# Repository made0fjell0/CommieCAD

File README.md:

<!-- PROJECT LOGO -->
<br />
<div align="center">

<h3 align="center">CommieCAD</h3>

  <p align="center">
    A custom CAD controller (intended for Fusion360) make using <a href="https://hackpad.hackclub.com">Hackpad</a>!
    <br />
    <br />
  </p>
</div>

<!-- TABLE OF CONTENTS -->
<details>
  <summary>Table of Contents</summary>
  <ol>
    <li>
      <a href="#about-the-project">About The Project</a>
    </li>
    <li>
      <a href="#How to">How to</a>
      <ul>
        <li><a href="#PCB">PCB</a></li>
        <li><a href="#Assembly">Assembly</a></li>
        <li><a href="#Code">Code</a></li>
      </ul>
    </li>
    <li><a href="#license">License</a></li>
  </ol>
</details>

<!-- ABOUT THE PROJECT -->
## About The Project

I had a need for an assistant to help me with design work in Fusion360 because using a touchpad to clumsily navigate around my parts forever is not very nice. This controller will have the following functions: **Orbit/Pan with joystick, zoom with rotary encoder, F, E and C keys for easy hotkey access.**

<!-- GETTING STARTED -->
## How to

First, you will have to 3d print a two part <a href="https://github.com/made0fjell0/CommieCAD/tree/main/STLs">case</a>.

You also need to print a simple <a href="https://github.com/made0fjell0/CommieCAD/blob/main/STLs/Joiner.stl">connective piece</a> between the encoder and joystick.

**IF YOU WANT TO** support me on printables, you can also find the STLs <a href="https://www.printables.com/model/1827930-commiecad">here</a>.

### PCB
**PCB-Less version coming SOON**<br>
The gerbers are <a href="https://github.com/made0fjell0/CommieCAD/tree/main/gerbers">HERE</a> and their compressed version <a href="https://github.com/made0fjell0/CommieCAD/tree/main/production/gerbers.zip">HERE.</a>
<br>
You can get the board cut from <a href="https://jlcpcb.com/pcb-fabrication/fr4-pcb">JLCPCB</a> probably for under 10 or 15$. Just sumbit the <a href="https://github.com/made0fjell0/CommieCAD/raw/refs/heads/main/production/gerbers.zip?raw=true">zip file</a> and they will cut it.
<br><br>
**Schematic**

### Assembly

First, you need to consult the <a href="https://github.com/made0fjell0/CommieCAD/blob/main/BOM.csv">BOM</a> (open it in excel) and get all the necesarry parts.
<br>
| Item Name                           | Qty | Price (total) (EUR) | Item link                                                                                                                                                                                                                                                                                                                                                                                                                                                                                                                                                                                                                                                                     |
|-------------------------------------|-----|---------------------|-------------------------------------------------------------------------------------------------------------------------------------------------------------------------------------------------------------------------------------------------------------------------------------------------------------------------------------------------------------------------------------------------------------------------------------------------------------------------------------------------------------------------------------------------------------------------------------------------------------------------------------------------------------------------------|
| 10-piece Cherry MX Brown switch kit | 1   | $4.58               | https://www.aliexpress.com/item/1005007891400560.html?spm=a2g0o.productlist.main.1.6632471082oz75&algo_pvid=cc87eb31-2a04-4b75-8094-35904d8a1e38&algo_exp_id=cc87eb31-2a04-4b75-8094-35904d8a1e38-0&pdp_ext_f=%7B"order"%3A"548"%2C"spu_best_type"%3A"price"%2C"eval"%3A"1"%2C"fromPage"%3A"search"%7D&pdp_npi=6%40dis%21EUR%214.58%214.58%21%21%2134.98%2134.98%21%4021613b2717880804173645049e10b2%2112000042740647794%21sea%21SK%216159834576%21X%211%210%21n_tag%3A-29919%3Bd%3A96cef531%3Bm03_new_user%3A-29895&curPageLogUid=I1Bh7Q49Hqvc&utparam-url=scene%3Asearch%7Cquery_from%3A%7Cx_object_id%3A1005007891400560%7C_p_origin_prod%3A                               |
| EC11 Rotary Encoder                 | 1   | $2.21               | https://www.aliexpress.com/item/1005006761212564.html?spm=a2g0o.productlist.main.50.29da2f4feu9XAI&algo_pvid=f01df35c-01d2-4d27-9c51-af2cd1076af7&algo_exp_id=f01df35c-01d2-4d27-9c51-af2cd1076af7-49&pdp_ext_f=%7B"order"%3A"107"%2C"eval"%3A"1"%2C"fromPage"%3A"search"%7D&pdp_npi=6%40dis%21EUR%211.67%211.67%21%21%2112.73%2112.72%21%402103962917880806218548881e10ef%2112000038303345963%21sea%21SK%216159834576%21X%211%210%21n_tag%3A-29919%3Bd%3A96cef531%3Bm03_new_user%3A-29895&curPageLogUid=YS14es0NDtm3&utparam-url=scene%3Asearch%7Cquery_from%3A%7Cx_object_id%3A1005006761212564%7C_p_origin_prod%3A                                                         |
| Joystick                            | 1   | $1.88               | https://www.aliexpress.com/item/1005008937490649.html?spm=a2g0o.productlist.main.21.3da072ecLABGBB&algo_pvid=135f1916-67c1-4bf8-8561-105024952dd0&algo_exp_id=135f1916-67c1-4bf8-8561-105024952dd0-20&pdp_ext_f=%7B"order"%3A"3448"%2C"spu_best_type"%3A"price"%2C"eval"%3A"1"%2C"fromPage"%3A"search"%7D&pdp_npi=6%40dis%21EUR%212.40%212.33%21%21%2118.36%2117.81%21%40210381f017880808031036287e0ea1%2112000047277002614%21sea%21SK%216159834576%21X%211%210%21n_tag%3A-29919%3Bd%3A96cef531%3Bm03_new_user%3A-29895%3BpisId%3A5000000215888387&curPageLogUid=N5SeqCFrkKCS&utparam-url=scene%3Asearch%7Cquery_from%3A%7Cx_object_id%3A1005008937490649%7C_p_origin_prod%3A |
| Keycaps                             | 3   | N/A                 | Find any set you like or get some spares from a keyboard.                                                                                                                                                                                                                                                                                                                                                                                                                                                                                                                                                                                                                     |
| Seeedstudio XIAO RP2040             | 1   | $3.99               | https://www.seeedstudio.com/XIAO-RP2040-v1-0-p-5026.html                                                                                                                                                                                                                                                                                                                                                                                                                                                                                                                                                                                                                      |
| M3 Screws 25mm screws               | 4   | $5.25               |                                                                                                                                                                                                                                                                                                                                                                                                                                                                                                                                                                                                                                                                               |
| Total Price (EUR): 17.91€           |     |                     |                                                                                                                                                                                                                                                                                                                                                                                                                                                                                                                                                                                                                                                                               |
<br>
Let the assembly begin: <br>
1. Place your seeeduino xiao on its designated space on the PCB. Carefully use small amounts of solder to bind each pad to the pads on the board.

2. Flip the board upside down and put the joystick into its spot. Solder each of its pins to the golden pads on the circuit board.

3. Still upside down, put in you switches and also solder their pins in place.

4. Flip the PCB back. Use 5 slim wires and solder them in the 5 broken out pads on the board. Solder these to the pins on your encoder. (designations will be added later along with build photos)

5. Glue the joiner piece to the bottom of the encoder and attach it onto the rod of the joystick.

6. Grab your M3 screws and put the case on.

## Code

**PLEASE take the code part with a grain of salt as it is not finished and was mostly done by ChatGPT**
<br><br>
You will need the <a href="https://www.arduino.cc/en/software/">ArduinoIDE</a>.
<br>
Download <a href="https://github.com/made0fjell0/CommieCAD/blob/main/Firmware/CommieCAD.ino">CommieCAD.ino</a>, open up Arduino IDE, plug in your seeeduino board and flash the code onto it. That's it, nice and easy.

## End

You should now be sucessfully done with building your very own **CommieCAD**! Hopefully it serves you well and helps you with many projects just like it.

<!-- LICENSE -->
## License

Distributed under the MIT license. See `LICENSE.txt` for more information.

<p align="right">(<a href="#readme-top">back to top</a>)</p>

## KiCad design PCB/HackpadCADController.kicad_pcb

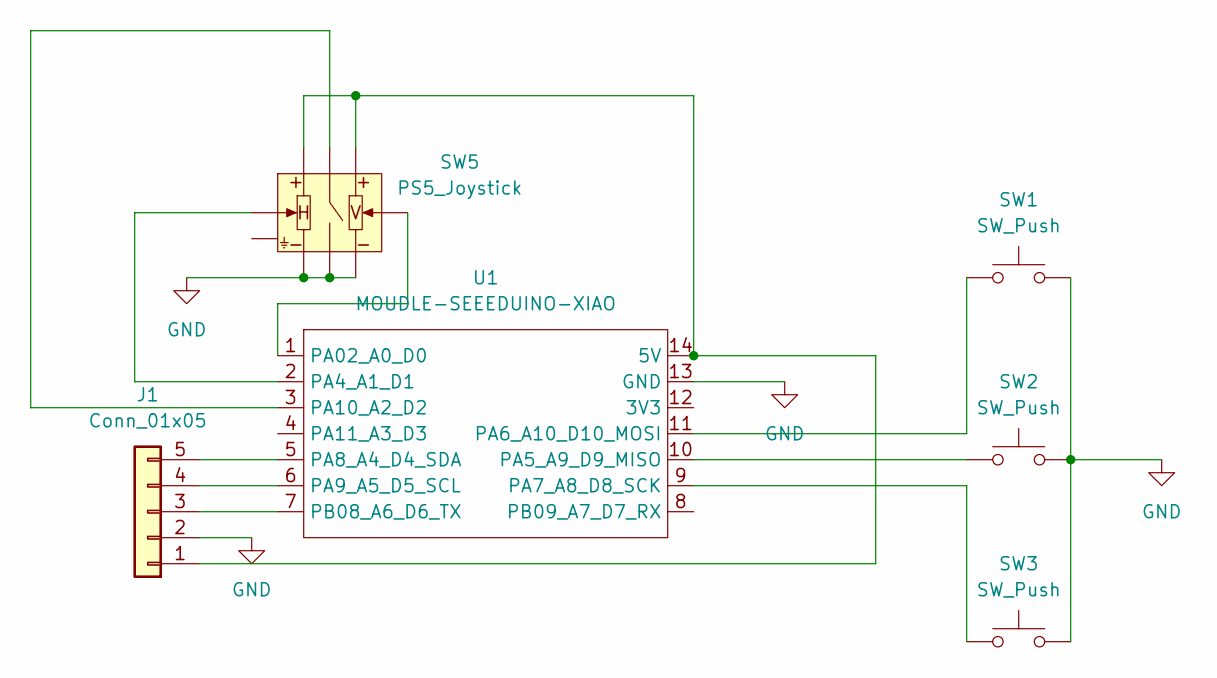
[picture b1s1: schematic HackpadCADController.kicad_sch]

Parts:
J1: Conn_01x05; PinHeader_1x05_P1.00mm_Vertical
SW1, SW2, SW3: SW_Push; SW_Cherry_MX_1.00u_PCB
SW5: PS5_Joystick
U1: MOUDLE-SEEEDUINO-XIAO; XIAO-Generic-Hybrid-14P-2.54-21X17.8MM

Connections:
GND: J1.2, SW1.2, SW2.2, SW3.2, SW5.1 (H-), SW5.1' (V-), SW5.c (BTN), SW5.d (BTN), U1.13 (GND)
unnamed: J1.1, SW5.3 (H+), SW5.3' (V+), U1.14 (5V)
unnamed: J1.3, U1.7 (PB08_A6_D6_TX)
unnamed: J1.4, U1.6 (PA9_A5_D5_SCL)
unnamed: J1.5, U1.5 (PA8_A4_D4_SDA)
unnamed: SW5.2 (H), U1.2 (PA4_A1_D1)
unnamed: SW5.2' (V), U1.1 (PA02_A0_D0)
unnamed: SW2.1, U1.10 (PA5_A9_D9_MISO)
unnamed: SW1.1, U1.11 (PA6_A10_D10_MOSI)
unnamed: SW3.1, U1.9 (PA7_A8_D8_SCK)
unnamed: SW5.a (BTN), SW5.b (BTN), U1.3 (PA10_A2_D2)

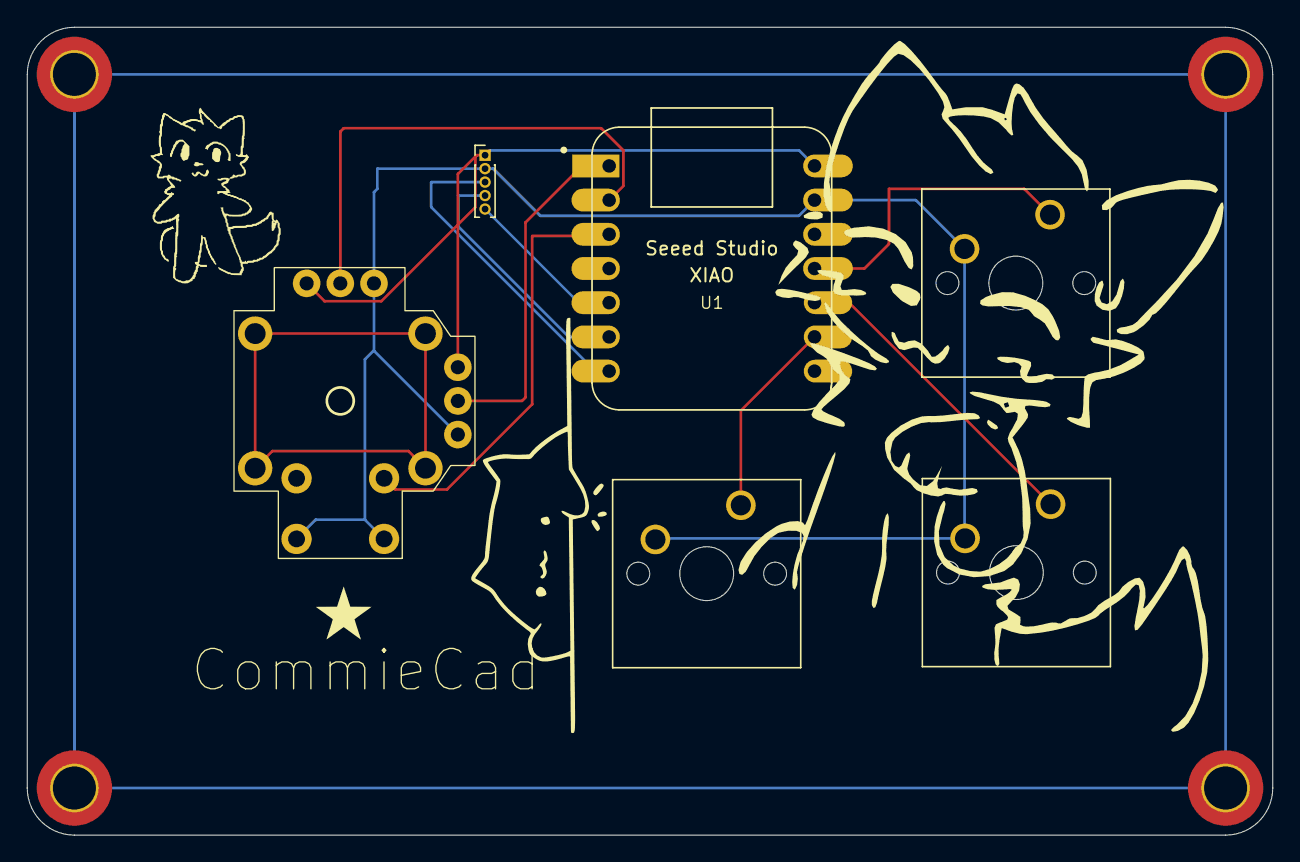
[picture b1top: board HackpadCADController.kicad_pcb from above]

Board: 2 copper layers, 92.5 x 60.0 mm, 6 parts (0 on the bottom side), 11 nets.
